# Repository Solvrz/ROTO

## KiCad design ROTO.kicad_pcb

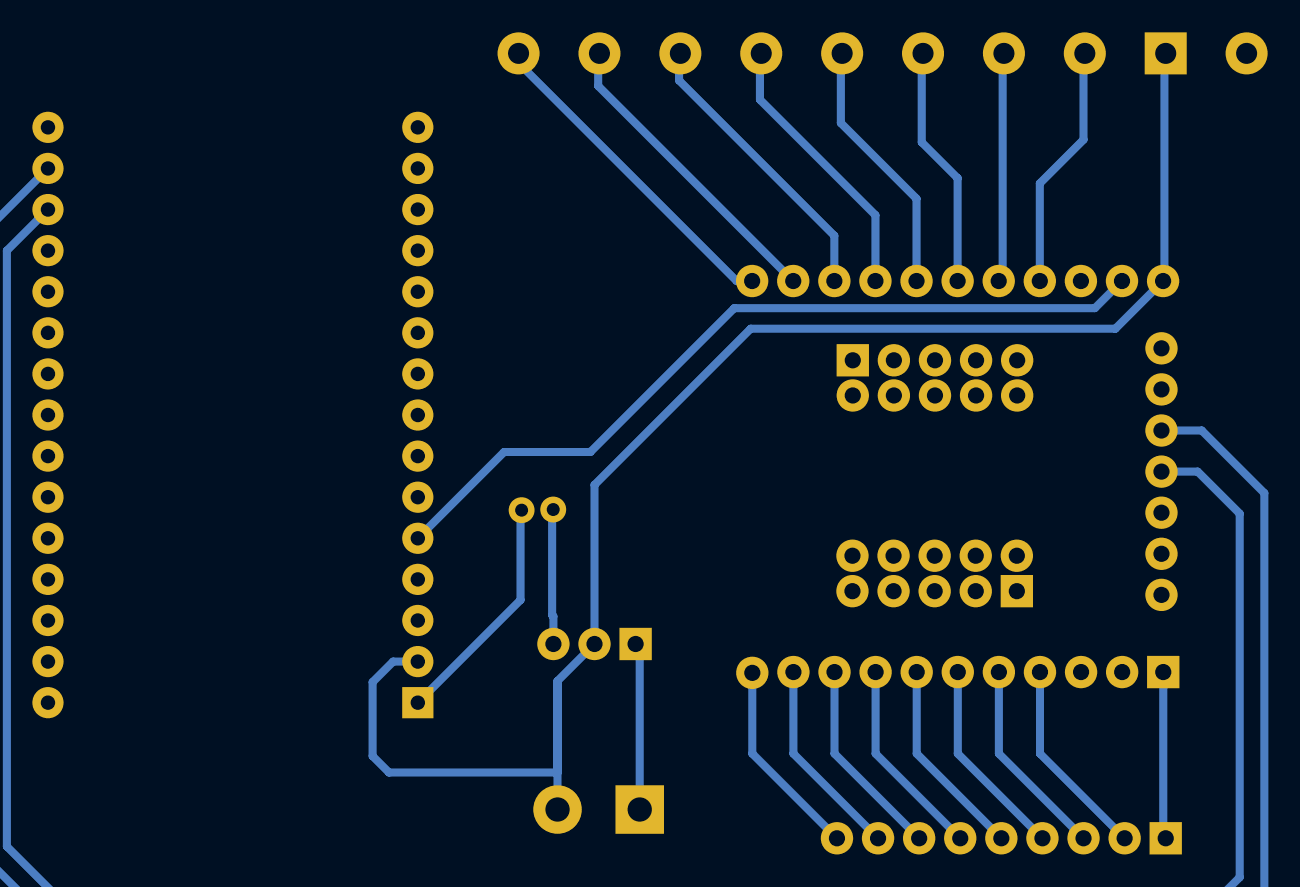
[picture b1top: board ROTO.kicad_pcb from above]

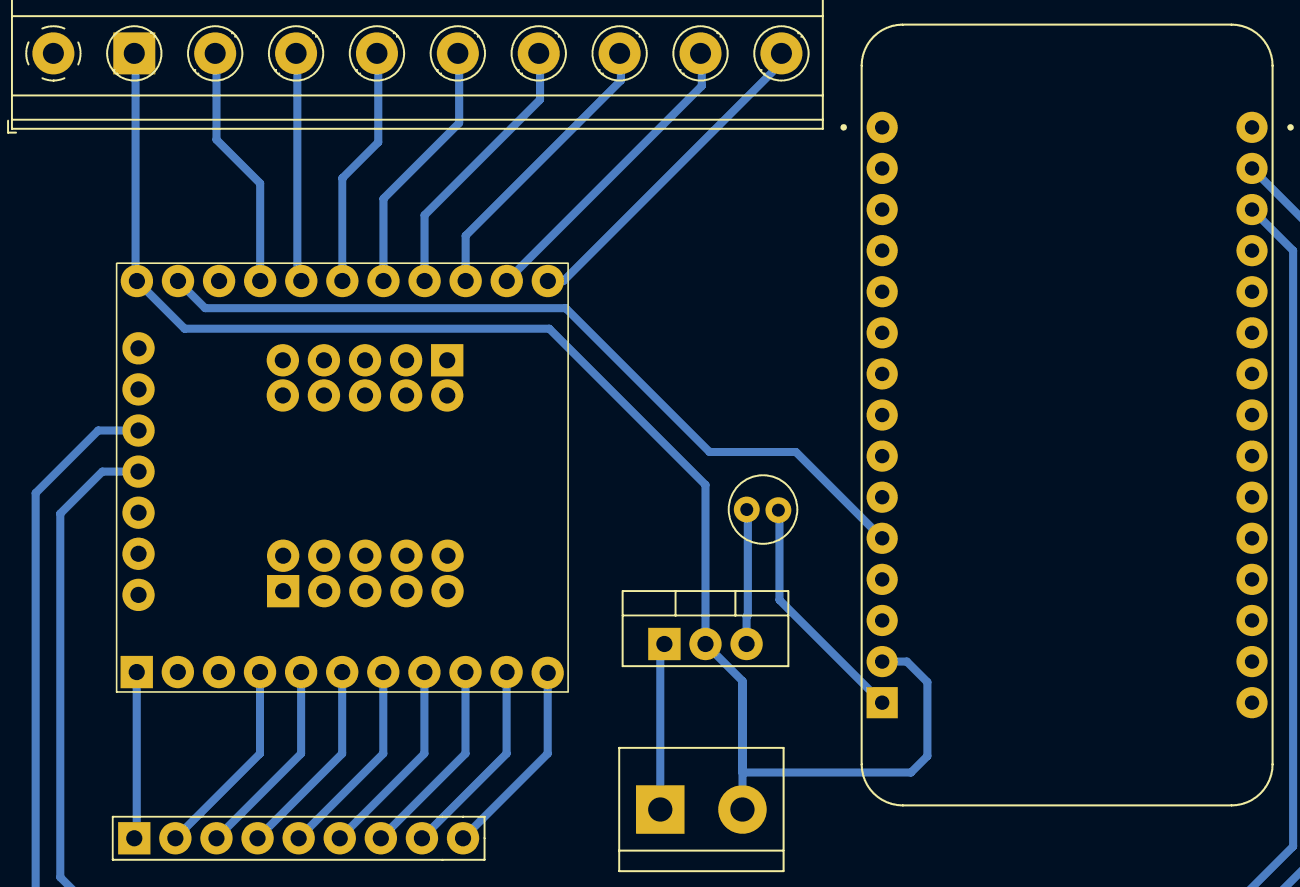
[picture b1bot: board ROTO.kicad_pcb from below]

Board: 2 copper layers, 7 parts (7 on the bottom side), 23 nets.

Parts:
A1: NODEMCU; MCU_NODEMCU
C1: C; C_Radial_D4.0mm_H7.0mm_P1.50mm
J1: POWER INPUT; TerminalBlock_bornier-2_P5.08mm
J2: RELAY; PinHeader_1x09_P2.54mm_Vertical
J3: Switch; TerminalBlock_Phoenix_MKDS-1,5-10_1x10_P5.00mm_Horizontal
U1: LM7805; TO-220-3_Vertical
U2: SX1509; MCU_SX1509

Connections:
+3.3V: A1.J1_11 (3V3), U2.28 (3.3V)
+5V: A1.J1_15 (VIN), C1.2
+12V: J1.1, U1.1 (VI)
GND: A1.J1_10 (GND), A1.J1_14 (GND), J1.2, J2.9, J3.2, U1.2 (GND), U2.27 (GND)
unnamed: A1.J2_2 (D1), U2.20 (SDA)
unnamed: A1.J2_3 (D2), U2.21 (SCL)
unnamed: J2.1, U2.11 (7)
unnamed: J2.2, U2.10 (6)
unnamed: J2.3, U2.9 (5)
unnamed: J2.4, U2.8 (4)
unnamed: J2.5, U2.7 (3)
unnamed: J2.6, U2.6 (2)
unnamed: J2.7, U2.5 (1)
unnamed: J2.8, U2.4 (0)
unnamed: J3.3, U2.19 (15)
unnamed: J3.4, U2.18 (14)
unnamed: J3.5, U2.17 (13)
unnamed: J3.6, U2.16 (12)
unnamed: J3.7, U2.15 (11)
unnamed: J3.8, U2.14 (10)
unnamed: J3.9, U2.13 (9)
unnamed: J3.10, U2.12 (8)
unnamed: C1.1, U1.3 (VO)

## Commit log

2023-05-20 Added README
2023-05-20 Updated REEADME
2023-05-24 Flipped PCB
2023-05-24 Updated PDF
